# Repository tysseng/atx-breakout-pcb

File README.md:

# atx-breakout-pcb

## Overview:
24p atx has:
- 4 x 3.3v
- 4 x 5v
- 2 x 12V1
- 1 x -12V
- 1 x -5V
- 8 x GND/COM
- 1 x 5V standby (always on)
- 1 x PS on
- 1 x PWR OK

Each channel: MAX 6A

## Initial spec from Stig-Rune:
- 24p ATX molex IN
- ATX motherboard power connector (Molex Mini-fit Jr. 39-28-1203,[7] former 5566-20A or 39-28-1243,[8] former 5566-24A)

### Eksponere pin som aktiverer PSU
- Vil du også ha en knapp på kortet? 
  <- nei, men om denne eksponeres som en 2p header så kan jeg putte en jumper der initielt, eller lodde på en av de kontaktene vi har på skuret
  -- Tenker jeg lager plass nok til en knapp likevel jeg, hvis det er plass :-D

### Eksponere pin som gir 5v når PSU er stabil
- Hva slags connector <- tenkte vanlig 2p header, så kan jeg enten bruke pins eller en 2p kontakt fra skuret
- Auto-start av Mosfets via jumper, see channel.

### Eksponere 5v standby
- Hva slags connector? <- igjen tenkte jeg å bruke vanlig pin-headers

### Eksponere 4x standard fan headere (12v + pwm + rpm), hvor pwm og rpm pins er eksponert et sted slik at jeg kan styre pwm og lese rpm med rpi eller arduino
- 12V fra en av kanalene, 8 I/O-pinner?  :+1:
- Bruke 10p IDC connector med GND og 5V i tillegg? <- høres ikke dumt ut :)

### Eksponere 4x USB-kontakter, 
- gjerne med 5A sikringer og noe som sørger for god strømlevering. 
- Kanskje også kontrollere disse via mosfets og eksponere pins for å styre dem, på en måte som lar meg sette på jumper for å enable kontaktene permanent.

### Eksponere 12v og 5v som hull til XT30 og pin-headere
- Max amp for pin header - flere pins pr. connector for samme volt? <- XT30 takler opp til 30A, var denne jeg tenkte for 12v. tenkte pin headere for 5v som mest sannsynlig blir typ arduinoer osv, så lite strøm.
- Både V+ og GND

## Løsningsforslag

### Channels:
- Mosfet control
- Cooling ribs
- control pin exposed for RPI/Ard.
- Jumper or DIP-switch to override control pin
- Automatic power on after PWR OK goes hi - connected through jumper or DIP-SWITCH 
- Indicator LED? After MOSFET
- 5A Fuse
- Filter and buffer caps
- pins and XT30 connector per channel, top mounted
- USB for 5V channel, edge mounted (?)
- Screw terminals for 12V (and others?)

- Shared 10p or 16p IDC connector depending on how many channels we want to expose (12 available)
	- OR use SPI with port expander chip to reduce the number of wires needed.
- 16p has room for 12 channels, gnd, 5v always on, ps on and pwr ok.
- May combine with 8-10p for fan control.
	- make pin-compatible with Raspberry? <- smart! jeg trenger ikke det tror jeg, men ser ikke noe grunn til å la vær fordet
	- May or may not use full 40p connector.

### Fan control
- 10p IDC for two pins/channel, GND, +5V
- Common 12v from the ATX PSU

## Research

ATX Pinouts:
- https://www.smpspowersupply.com/connectors-pinouts.html

Molex contact
- The P1 uses Molex Housing Mini-Fit Jr. P/N# 39-01-2240 style, motherboard header is Molex 44206-0007

Mosfet control
- Negative side: https://bildr.org/2012/03/rfp30n06le-arduino/
- Positive side, Vcc > 5v: https://www.gammon.com.au/motors

Other
- Minimum current requirement on 5V for startup? "From what i read an old powersupply which has more ampeeres on 
  the 5v side needs at least 1A of minimum current.... so i will prolly need 10ohm 10W dummy load"
- Expose as separate connector to connect power resistor if needed??

PCB track width
- Calculator: https://www.4pcb.com/trace-width-calculator.html
- 5A: 109 MIL w 1 oz copper, 55MIL w 2 oz ($20 extra at dirtypcbs)

USB
- Stacked connectors?
- All on the same side

FUSES
- miniature automotive fuses or resettable pcb-mounted fuses?
- https://www.edn.com/protecting-against-reverse-polarity-methods-examined-part-1/

Power on-led
Power good-led

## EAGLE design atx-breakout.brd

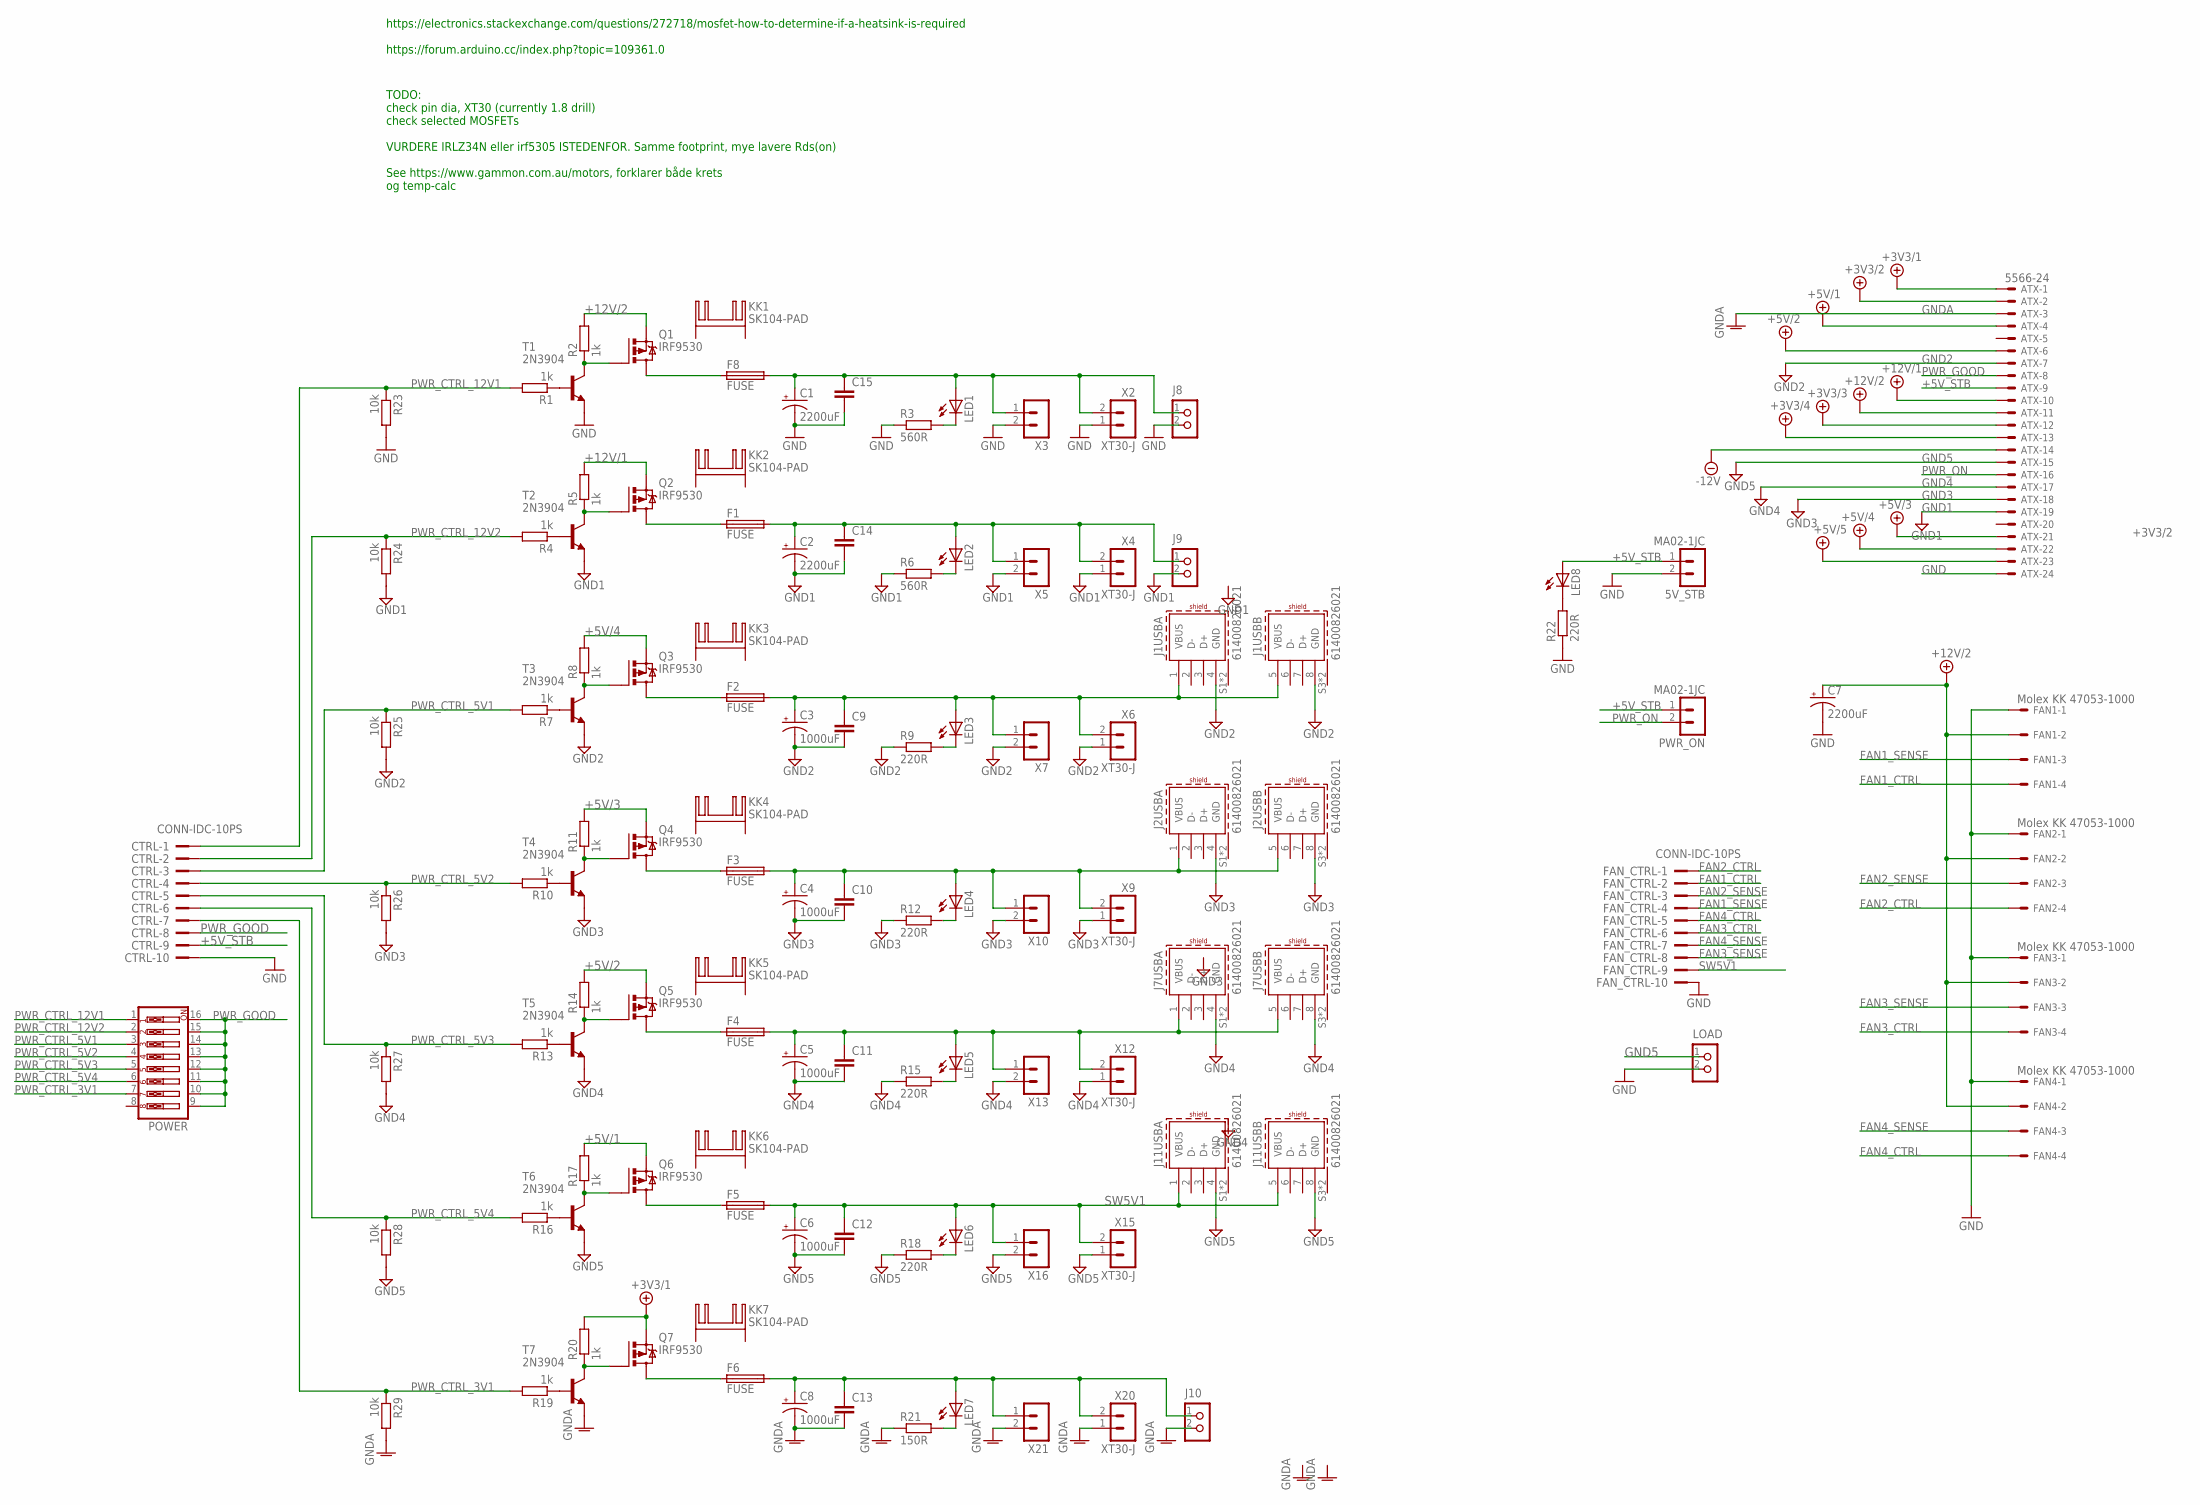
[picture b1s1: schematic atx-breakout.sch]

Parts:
5V_STB: MA02-1JC; MA02-1J
ATX: 5566-24
C1, C2, C7: 2200uF; E7,5-16
C3, C4, C5, C6, C8: 1000uF; E5-10,5
C9, C10, C11, C12, C13, C14, C15: C-EU050-030X075; C050-030X075
CTRL: CONN-IDC-10PS; CONN-IDC10P-S
F1, F2, F3, F4, F5, F6, F8: FUSE; FUSE_HOLDER_5X20MM
FAN1, FAN2, FAN3, FAN4: Molex KK 47053-1000; 6410-04
FAN_CTRL: CONN-IDC-10PS; CONN-IDC10P-S
J1, J2, J7, J11: 61400826021
J8, J9, J10: CON_TERMINAL_BLOCK_02-5MM; TERMINAL_BLOCK_2P_5
KK1, KK2, KK3, KK4, KK5, KK6, KK7: SK104-PAD
LED1, LED2, LED3, LED4, LED5, LED6, LED7, LED8: LED_J3MM; LED3MM
LOAD: CON_TERMINAL_BLOCK_02-5MM; TERMINAL_BLOCK_2P_5
POWER: SW_DIP-8; EDG-08
PWR_ON: MA02-1JC; MA02-1J
Q1, Q2, Q3, Q4, Q5, Q6, Q7: IRF9530; TO220BV
R1, R2, R4, R5, R7, R8, R10, R11, R13, R14, R16, R17, R19, R20: 1k; 0207/7
R3, R6: 560R; 0207/7
R9, R12, R15, R18, R22: 220R; 0207/7
R21: 150R; 0207/7
R23, R24, R25, R26, R27, R28, R29: 10k; 0207/7
T1, T2, T3, T4, T5, T6, T7: 2N3904; TO92
X2, X4, X6, X9, X12, X15, X20: XT30-J
X3, X5, X7, X10, X13, X16, X21: MA02-1JC; MA02-1J

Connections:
+3V3/1: ATX.1, Q7.S, R20.2
+3V3/2: ATX.2
+3V3/3: ATX.12
+3V3/4: ATX.13
+5V: ATX.23
+5V/1: ATX.4, Q6.S, R17.2
+5V/2: ATX.6, Q5.S, R14.2
+5V/3: ATX.21, Q4.S, R11.2
+5V/4: ATX.22, Q3.S, R8.2
+5V_STB: 5V_STB.1, ATX.9, CTRL.9, LED8.A, PWR_ON.1
+12V/1: ATX.10, Q2.S, R5.2
+12V/2: ATX.11, C7.+, FAN1.2, FAN2.2, FAN3.2, FAN4.2, Q1.S, R2.2
-12V: ATX.14
FAN1_CTRL: FAN1.4, FAN_CTRL.2
FAN1_SENSE: FAN1.3, FAN_CTRL.4
FAN2_CTRL: FAN2.4, FAN_CTRL.1
FAN2_SENSE: FAN2.3, FAN_CTRL.3
FAN3_CTRL: FAN3.4, FAN_CTRL.6
FAN3_SENSE: FAN3.3, FAN_CTRL.8
FAN4_CTRL: FAN4.4, FAN_CTRL.5
FAN4_SENSE: FAN4.3, FAN_CTRL.7
GND: 5V_STB.2, ATX.24, C1.-, C7.-, C15.2, CTRL.10, FAN1.1, FAN2.1, FAN3.1, FAN4.1, FAN_CTRL.10, J8.2, LOAD.2, R3.1, R22.1, R23.2, T1.3 (E), X2.1, X3.2
GND1: ATX.19, C2.-, C14.2, J9.2, R6.1, R24.2, T2.3 (E), X4.1, X5.2
GND2: ATX.7, C3.-, C9.2, J1.4 (GND), J1.8 (GND), R9.1, R25.2, T3.3 (E), X6.1, X7.2
GND3: ATX.18, C4.-, C10.2, J2.4 (GND), J2.8 (GND), R12.1, R26.2, T4.3 (E), X9.1, X10.2
GND4: ATX.17, C5.-, C11.2, J7.4 (GND), J7.8 (GND), R15.1, R27.2, T5.3 (E), X12.1, X13.2
GND5: ATX.15, C6.-, C12.2, J11.4 (GND), J11.8 (GND), LOAD.1, R18.1, R28.2, T6.3 (E), X15.1, X16.2
GNDA: ATX.3, C8.-, C13.2, J10.2, R21.1, R29.2, T7.3 (E), X20.1, X21.2
unnamed: R1.1, T1.2 (B)
unnamed: Q1.G, R2.1, T1.1 (C)
unnamed: LED8.K (C), R22.2
unnamed: C1.+, C15.1, F8.2, J8.1, LED1.A, X2.2, X3.1
unnamed: LED1.K (C), R3.2
unnamed: F8.1, Q1.D
unnamed: R4.1, T2.2 (B)
unnamed: Q2.G, R5.1, T2.1 (C)
unnamed: C2.+, C14.1, F1.2, J9.1, LED2.A, X4.2, X5.1
unnamed: LED2.K (C), R6.2
unnamed: F1.1, Q2.D
unnamed: R7.1, T3.2 (B)
unnamed: Q3.G, R8.1, T3.1 (C)
unnamed: C3.+, C9.1, F2.2, J1.1 (VBUS), J1.5 (VBUS), LED3.A, X6.2, X7.1
unnamed: LED3.K (C), R9.2
unnamed: F2.1, Q3.D
unnamed: R10.1, T4.2 (B)
unnamed: Q4.G, R11.1, T4.1 (C)
unnamed: C4.+, C10.1, F3.2, J2.1 (VBUS), J2.5 (VBUS), LED4.A, X9.2, X10.1
unnamed: LED4.K (C), R12.2
unnamed: F3.1, Q4.D
unnamed: R13.1, T5.2 (B)
unnamed: Q5.G, R14.1, T5.1 (C)
unnamed: C5.+, C11.1, F4.2, J7.1 (VBUS), J7.5 (VBUS), LED5.A, X12.2, X13.1
unnamed: LED5.K (C), R15.2
unnamed: F4.1, Q5.D
unnamed: R16.1, T6.2 (B)
unnamed: Q6.G, R17.1, T6.1 (C)
unnamed: LED6.K (C), R18.2
unnamed: F5.1, Q6.D
unnamed: R19.1, T7.2 (B)
unnamed: Q7.G, R20.1, T7.1 (C)
unnamed: C8.+, C13.1, F6.2, J10.1, LED7.A, X20.2, X21.1
unnamed: LED7.K (C), R21.2
unnamed: F6.1, Q7.D
PWR_CTRL_3V1: CTRL.7, POWER.7, R19.2, R29.1
PWR_CTRL_5V1: CTRL.3, POWER.3, R7.2, R25.1
PWR_CTRL_5V2: CTRL.4, POWER.4, R10.2, R26.1
PWR_CTRL_5V3: CTRL.5, POWER.5, R13.2, R27.1
PWR_CTRL_5V4: CTRL.6, POWER.6, R16.2, R28.1
PWR_CTRL_12V1: CTRL.1, POWER.1, R1.2, R23.1
PWR_CTRL_12V2: CTRL.2, POWER.2, R4.2, R24.1
PWR_GOOD: ATX.8, CTRL.8, POWER.9, POWER.10, POWER.11, POWER.12, POWER.13, POWER.14, POWER.15, POWER.16
PWR_ON: ATX.16, PWR_ON.2
SW5V1: C6.+, C12.1, F5.2, FAN_CTRL.9, J11.1 (VBUS), J11.5 (VBUS), LED6.A, X15.2, X16.1

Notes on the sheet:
TODO: check pin dia, XT30 (currently 1.8 drill) check selected MOSFETs VURDERE IRLZ34N eller irf5305 ISTEDENFOR. Samme footprint, mye lavere Rds(on) See https://www.gammon.com.au/motors, forklarer både krets og temp-calc
https://electronics.stackexchange.com/questions/272718/mosfet-how-to-determine-if-a-heatsink-is-required https://forum.arduino.cc/index.php?topic=109361.0

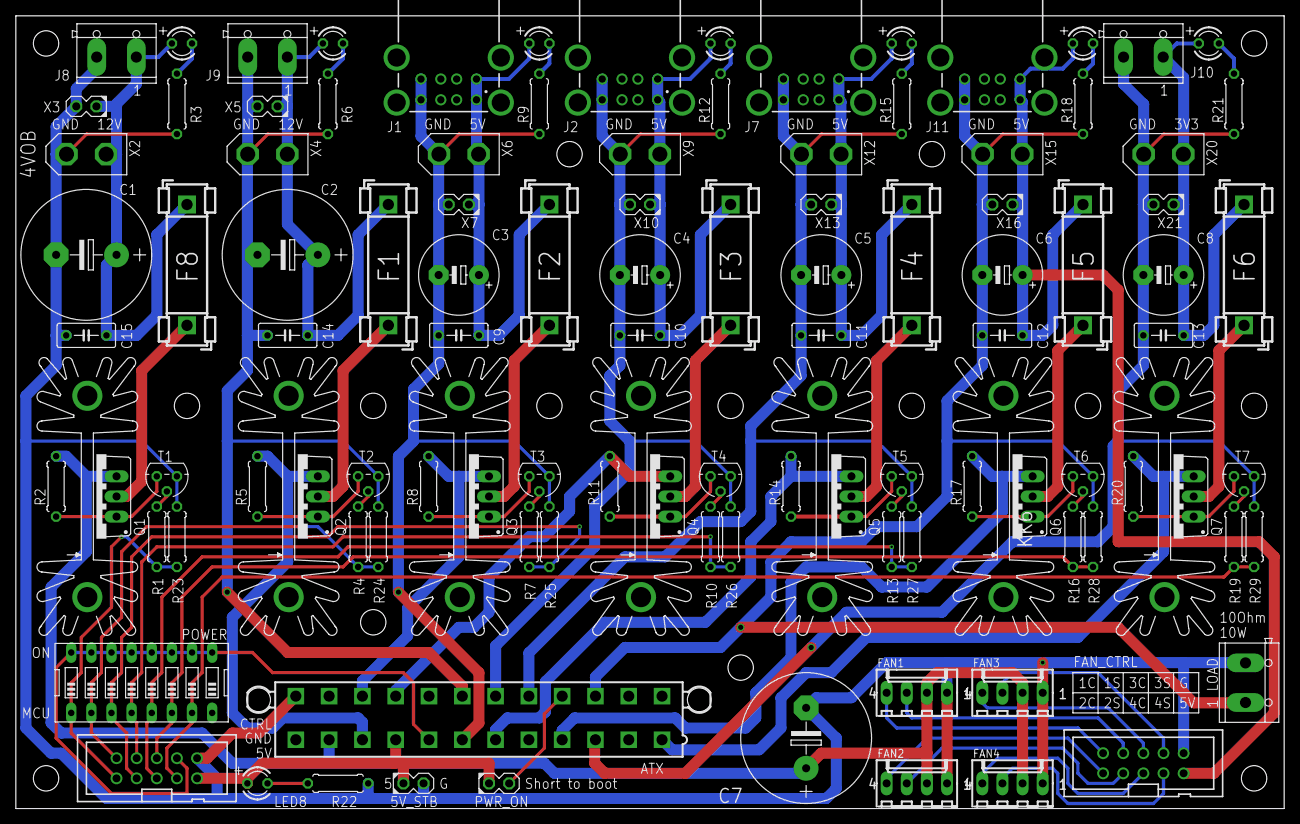
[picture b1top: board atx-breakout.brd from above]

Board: 2 copper layers, 160.0 x 100.0 mm, 113 parts (1 on the bottom side), 68 nets.

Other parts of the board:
U$1: XONIK_LOGO_60

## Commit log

2020-10-29 Added initial thoughts
2020-10-29 Added more thoughts
2020-10-29 Update README.md
    Added some responses
2020-10-31 Added ATX connector
2020-11-01 Six channel version, initial layout
2020-11-07 Added 3v3, control header, fan control headers, extra room for filter cap
2020-11-07 More cleanup, made room for screws etc
2020-11-07 Everything routed, but need to rething GND
2020-11-08 Separate grounds for every channel
2020-11-09 More mounting holes, screw terminal for 10Ohm load
2020-11-18 Updated XT-30 footprint, updated pulldown resistor value

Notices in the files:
parts and their libraries:
Wurth_Connectors_WR-USB: Copyright: Würth Elektronik
